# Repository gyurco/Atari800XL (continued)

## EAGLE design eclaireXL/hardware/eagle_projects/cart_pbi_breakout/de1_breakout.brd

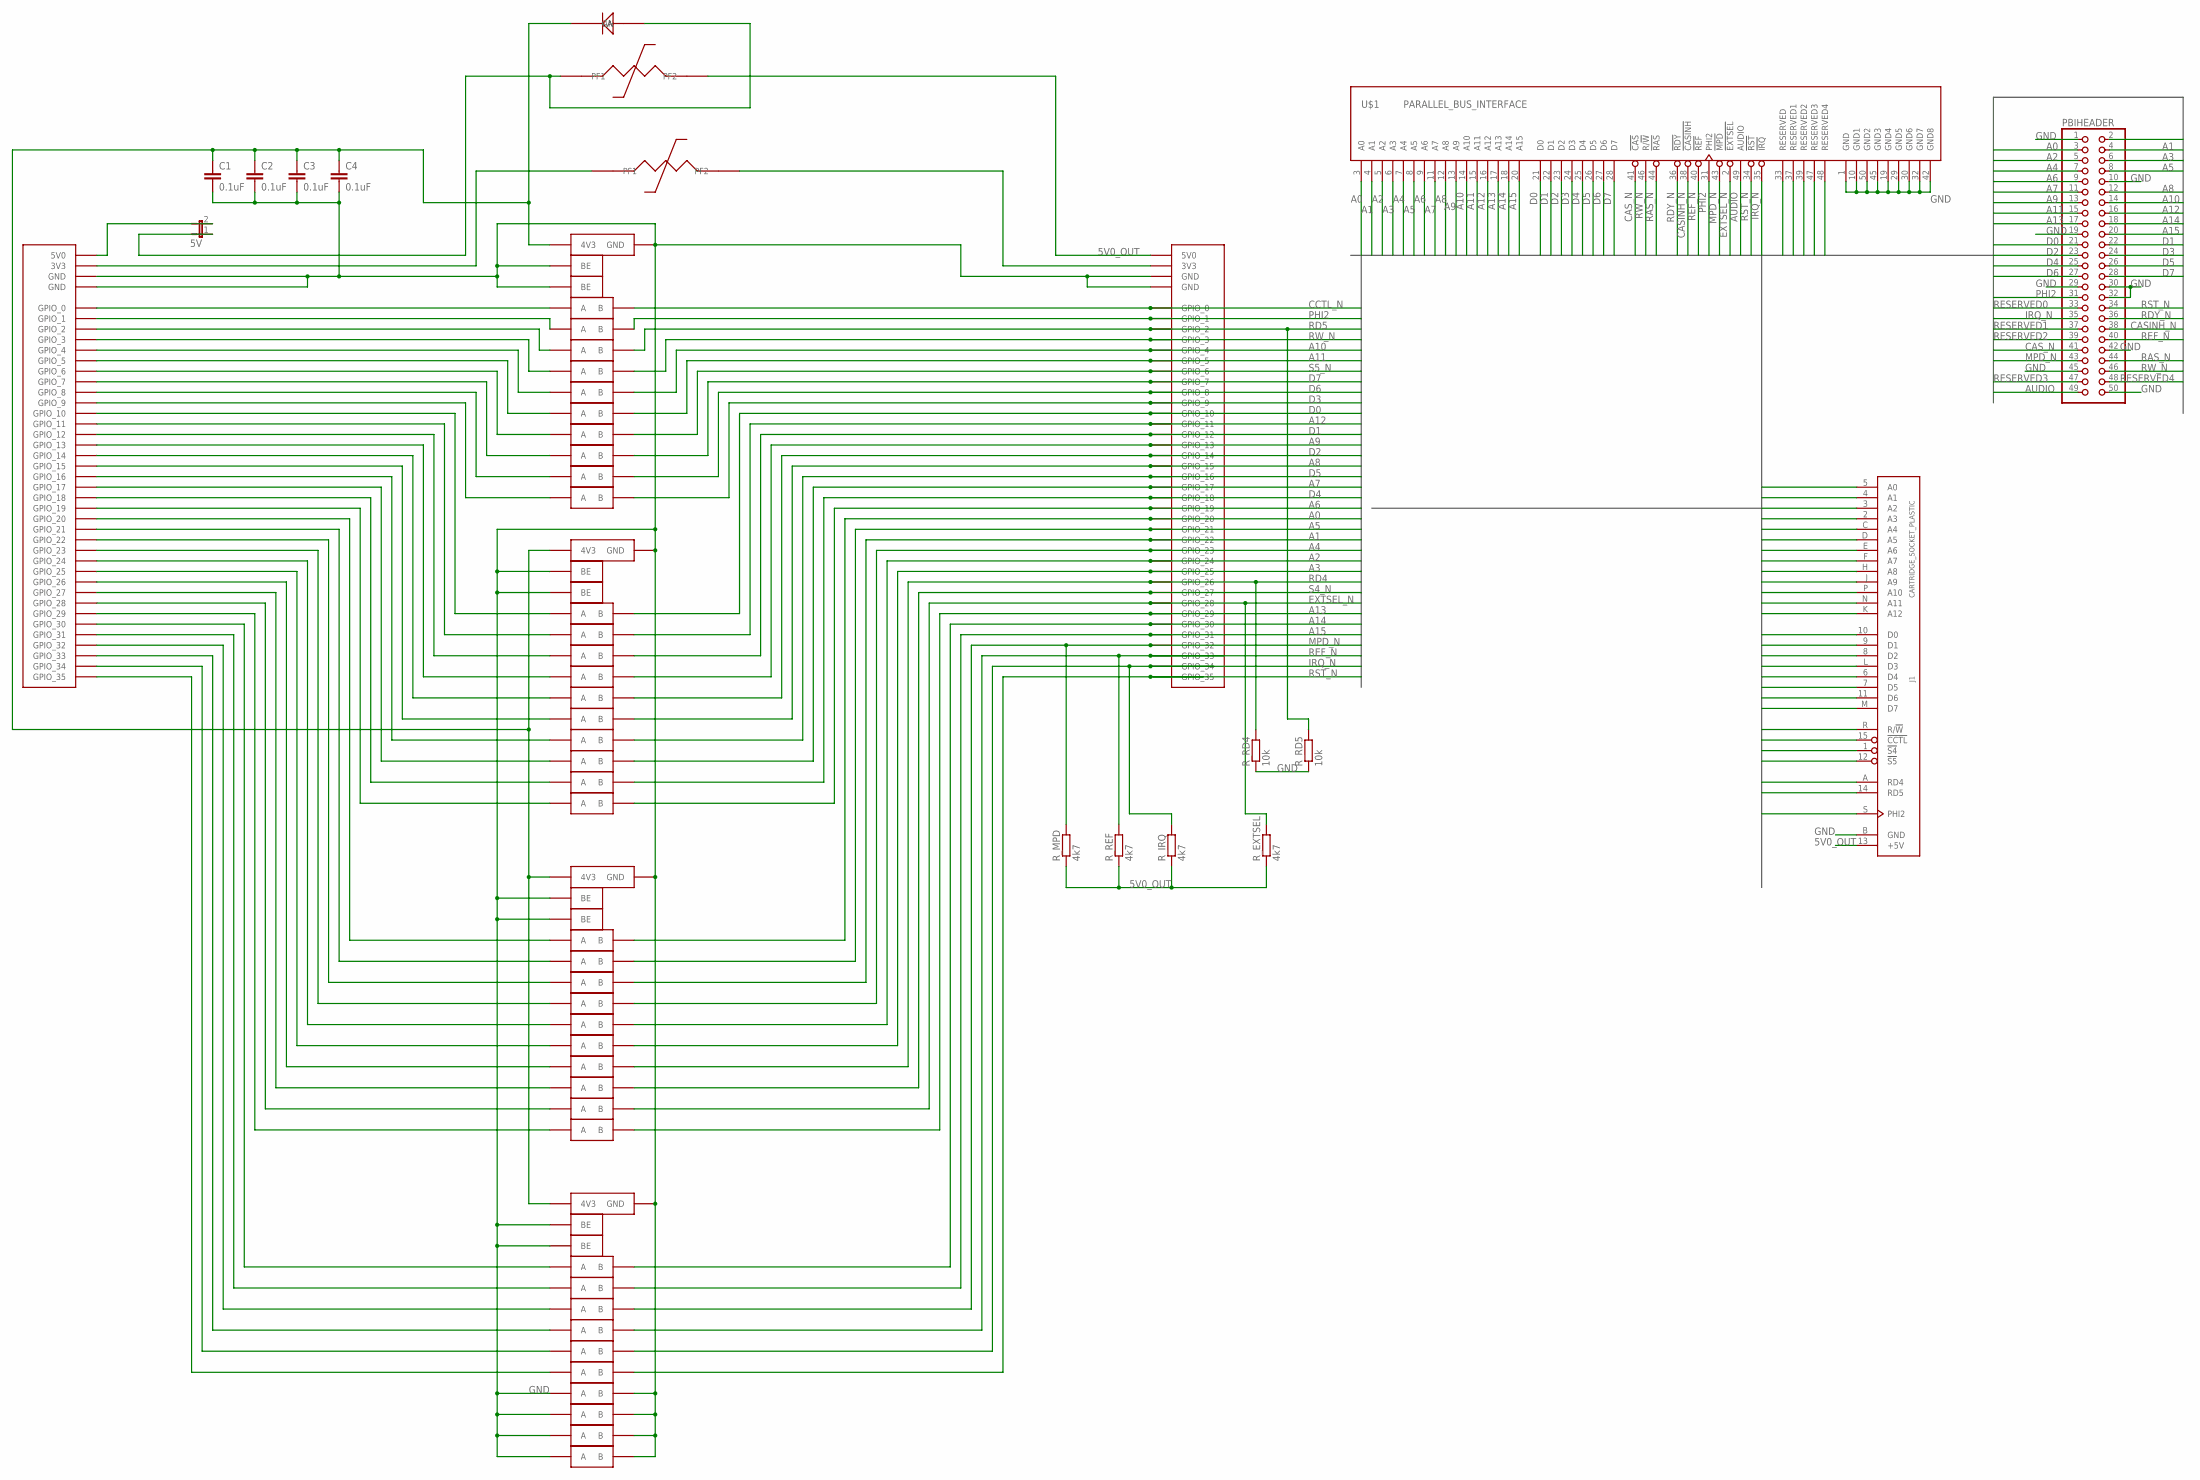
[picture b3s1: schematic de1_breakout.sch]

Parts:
1N4148: 1N4148; SOD123
3VPOLY, 5VPOLY: POLYFUSE_1206; C1206
5V: JP1E; JP1
C1, C2, C3, C4: 0.1uF; C1206
DE1_GPIO: DE1_GPIO; DIL-100-2X20
EXT_GPIO: DE1_GPIO_L; DIL-100-2X20
IC1, IC2, IC3, IC4: QS3384; TSSOP24
J1: CARTRIDGE_SOCKET_PLASTIC; CARTRIDGE_SOCKET_WITH_PLASTIC
PBIHEADER: PINHD-2X25; 2X25
R_EXTSEL: 4k7; R1206
R_IRQ: 4k7; R1206
R_MPD: 4k7; R1206
R_RD4, R_RD5: 10k; R1206
R_REF: 4k7; R1206
U$1: PARALLEL_BUS_INTERFACE

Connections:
3V3_IN: 3VPOLY.1 (PF1), DE1_GPIO.29 (3V3)
3V3_OUT: 3VPOLY.2 (PF2), EXT_GPIO.29 (3V3)
4V3_INT: 1N4148.1 (CA), C1.1, C2.1, C3.1, C4.1, IC1.24 (4V3), IC2.24 (4V3), IC3.24 (4V3), IC4.24 (4V3)
5V0_DE1: 5V.2, DE1_GPIO.11 (5V0)
5V0_IN: 1N4148.2 (AN), 5V.1, 5VPOLY.1 (PF1)
5V0_OUT: 5VPOLY.2 (PF2), EXT_GPIO.11 (5V0), J1.13 (+5V), R_EXTSEL.1, R_IRQ.1, R_MPD.1, R_REF.1
A0: EXT_GPIO.23 (GPIO_20), IC3.2 (B), J1.5 (A0), PBIHEADER.3, U$1.3 (A0)
A1: EXT_GPIO.25 (GPIO_22), IC3.6 (B), J1.4 (A1), PBIHEADER.4, U$1.4 (A1)
A2: EXT_GPIO.27 (GPIO_24), IC3.10 (B), J1.3 (A2), PBIHEADER.5, U$1.5 (A2)
A3: EXT_GPIO.28 (GPIO_25), IC3.15 (B), J1.2 (A3), PBIHEADER.6, U$1.6 (A3)
A4: EXT_GPIO.26 (GPIO_23), IC3.9 (B), J1.C (A4), PBIHEADER.7, U$1.7 (A4)
A5: EXT_GPIO.24 (GPIO_21), IC3.5 (B), J1.D (A5), PBIHEADER.8, U$1.8 (A5)
A6: EXT_GPIO.22 (GPIO_19), IC2.23 (B), J1.E (A6), PBIHEADER.9, U$1.9 (A6)
A7: EXT_GPIO.20 (GPIO_17), IC2.19 (B), J1.F (A7), PBIHEADER.11, U$1.11 (A7)
A8: EXT_GPIO.18 (GPIO_15), IC2.15 (B), J1.H (A8), PBIHEADER.12, U$1.12 (A8)
A9: EXT_GPIO.16 (GPIO_13), IC2.9 (B), J1.J (A9), PBIHEADER.13, U$1.13 (A9)
A10: EXT_GPIO.5 (GPIO_4), IC1.10 (B), J1.P (A10), PBIHEADER.14, U$1.14 (A10)
A11: EXT_GPIO.6 (GPIO_5), IC1.15 (B), J1.N (A11), PBIHEADER.15, U$1.15 (A11)
A12: EXT_GPIO.14 (GPIO_11), IC2.5 (B), J1.K (A12), PBIHEADER.16, U$1.16 (A12)
A13: EXT_GPIO.34 (GPIO_29), IC3.23 (B), PBIHEADER.17, U$1.17 (A13)
A14: EXT_GPIO.35 (GPIO_30), IC4.2 (B), PBIHEADER.18, U$1.18 (A14)
A15: EXT_GPIO.36 (GPIO_31), IC4.5 (B), PBIHEADER.20, U$1.20 (A15)
AUDIO: PBIHEADER.49, U$1.49 (AUDIO)
CASINH_N: PBIHEADER.38, U$1.38 (!CASINH)
CAS_N: PBIHEADER.41, U$1.41 (!CAS)
CCTL_N: EXT_GPIO.1 (GPIO_0), IC1.2 (B), J1.15 (!CCTL)
D0: EXT_GPIO.13 (GPIO_10), IC2.2 (B), J1.10 (D0), PBIHEADER.21, U$1.21 (D0)
D1: EXT_GPIO.15 (GPIO_12), IC2.6 (B), J1.9 (D1), PBIHEADER.22, U$1.22 (D1)
D2: EXT_GPIO.17 (GPIO_14), IC2.10 (B), J1.8 (D2), PBIHEADER.23, U$1.23 (D2)
D3: EXT_GPIO.10 (GPIO_9), IC1.23 (B), J1.L (D3), PBIHEADER.24, U$1.24 (D3)
D4: EXT_GPIO.21 (GPIO_18), IC2.20 (B), J1.6 (D4), PBIHEADER.25, U$1.25 (D4)
D5: EXT_GPIO.19 (GPIO_16), IC2.16 (B), J1.7 (D5), PBIHEADER.26, U$1.26 (D5)
D6: EXT_GPIO.9 (GPIO_8), IC1.20 (B), J1.11 (D6), PBIHEADER.27, U$1.27 (D6)
D7: EXT_GPIO.8 (GPIO_7), IC1.19 (B), J1.M (D7), PBIHEADER.28, U$1.28 (D7)
EXTSEL_N: EXT_GPIO.33 (GPIO_28), IC3.20 (B), PBIHEADER.2, R_EXTSEL.2, U$1.2 (!EXTSEL)
GND: C1.2, C2.2, C3.2, C4.2, DE1_GPIO.12 (GND), DE1_GPIO.30 (GND), EXT_GPIO.12 (GND), EXT_GPIO.30 (GND), IC1.1 (BE), IC1.12 (GND), IC1.13 (BE), IC2.1 (BE), IC2.12 (GND), IC2.13 (BE), IC3.1 (BE), IC3.12 (GND), IC3.13 (BE), IC4.1 (BE), IC4.12 (GND), IC4.13 (BE), IC4.16 (B), IC4.17 (A), IC4.18 (A), IC4.19 (B), IC4.20 (B), IC4.21 (A), IC4.22 (A), IC4.23 (B), J1.B (GND), PBIHEADER.1, PBIHEADER.10, PBIHEADER.19, PBIHEADER.29, PBIHEADER.30, PBIHEADER.32, PBIHEADER.42, PBIHEADER.45, PBIHEADER.50, R_RD4.1, R_RD5.1, U$1.1 (GND), U$1.10 (GND1), U$1.19 (GND4), U$1.29 (GND5), U$1.30 (GND6), U$1.32 (GND7), U$1.42 (GND8), U$1.45 (GND3), U$1.50 (GND2)
IRQ_N: EXT_GPIO.39 (GPIO_34), IC4.10 (B), PBIHEADER.35, R_IRQ.2, U$1.35 (!IRQ)
MPD_N: EXT_GPIO.37 (GPIO_32), IC4.6 (B), PBIHEADER.43, R_MPD.2, U$1.43 (!MPD)
unnamed: DE1_GPIO.1 (GPIO_0), IC1.3 (A)
unnamed: DE1_GPIO.2 (GPIO_1), IC1.4 (A)
unnamed: DE1_GPIO.3 (GPIO_2), IC1.7 (A)
unnamed: DE1_GPIO.4 (GPIO_3), IC1.8 (A)
unnamed: DE1_GPIO.5 (GPIO_4), IC1.11 (A)
unnamed: DE1_GPIO.6 (GPIO_5), IC1.14 (A)
unnamed: DE1_GPIO.7 (GPIO_6), IC1.17 (A)
unnamed: DE1_GPIO.8 (GPIO_7), IC1.18 (A)
unnamed: DE1_GPIO.9 (GPIO_8), IC1.21 (A)
unnamed: DE1_GPIO.10 (GPIO_9), IC1.22 (A)
unnamed: DE1_GPIO.13 (GPIO_10), IC2.3 (A)
unnamed: DE1_GPIO.14 (GPIO_11), IC2.4 (A)
unnamed: DE1_GPIO.15 (GPIO_12), IC2.7 (A)
unnamed: DE1_GPIO.16 (GPIO_13), IC2.8 (A)
unnamed: DE1_GPIO.17 (GPIO_14), IC2.11 (A)
unnamed: DE1_GPIO.18 (GPIO_15), IC2.14 (A)
unnamed: DE1_GPIO.19 (GPIO_16), IC2.17 (A)
unnamed: DE1_GPIO.20 (GPIO_17), IC2.18 (A)
unnamed: DE1_GPIO.21 (GPIO_18), IC2.21 (A)
unnamed: DE1_GPIO.22 (GPIO_19), IC2.22 (A)
unnamed: DE1_GPIO.23 (GPIO_20), IC3.3 (A)
unnamed: DE1_GPIO.24 (GPIO_21), IC3.4 (A)
unnamed: DE1_GPIO.25 (GPIO_22), IC3.7 (A)
unnamed: DE1_GPIO.26 (GPIO_23), IC3.8 (A)
unnamed: DE1_GPIO.27 (GPIO_24), IC3.11 (A)
unnamed: DE1_GPIO.28 (GPIO_25), IC3.14 (A)
unnamed: DE1_GPIO.31 (GPIO_26), IC3.17 (A)
unnamed: DE1_GPIO.32 (GPIO_27), IC3.18 (A)
unnamed: DE1_GPIO.33 (GPIO_28), IC3.21 (A)
unnamed: DE1_GPIO.34 (GPIO_29), IC3.22 (A)
unnamed: DE1_GPIO.37 (GPIO_32), IC4.7 (A)
unnamed: DE1_GPIO.35 (GPIO_30), IC4.3 (A)
unnamed: DE1_GPIO.36 (GPIO_31), IC4.4 (A)
unnamed: DE1_GPIO.38 (GPIO_33), IC4.8 (A)
unnamed: DE1_GPIO.39 (GPIO_34), IC4.11 (A)
unnamed: DE1_GPIO.40 (GPIO_35), IC4.14 (A)
PHI2: EXT_GPIO.2 (GPIO_1), IC1.5 (B), J1.S (PHI2), PBIHEADER.31, U$1.31 (PHI2)
RAS_N: PBIHEADER.44, U$1.44 (!RAS)
RD4: EXT_GPIO.31 (GPIO_26), IC3.16 (B), J1.A (RD4), R_RD4.2
RD5: EXT_GPIO.3 (GPIO_2), IC1.6 (B), J1.14 (RD5), R_RD5.2
RDY_N: PBIHEADER.36, U$1.36 (!RDY)
REF_N: EXT_GPIO.38 (GPIO_33), IC4.9 (B), PBIHEADER.40, R_REF.2, U$1.40 (!REF)
RESERVED0: PBIHEADER.33, U$1.33 (RESERVED)
RESERVED1: PBIHEADER.37, U$1.37 (RESERVED1)
RESERVED2: PBIHEADER.39, U$1.39 (RESERVED2)
RESERVED3: PBIHEADER.47, U$1.47 (RESERVED3)
RESERVED4: PBIHEADER.48, U$1.48 (RESERVED4)
RST_N: EXT_GPIO.40 (GPIO_35), IC4.15 (B), PBIHEADER.34, U$1.34 (!RST)
RW_N: EXT_GPIO.4 (GPIO_3), IC1.9 (B), J1.R (R/!W), PBIHEADER.46, U$1.46 (R/!W)
S4_N: EXT_GPIO.32 (GPIO_27), IC3.19 (B), J1.1 (!S4)
S5_N: EXT_GPIO.7 (GPIO_6), IC1.16 (B), J1.12 (!S5)

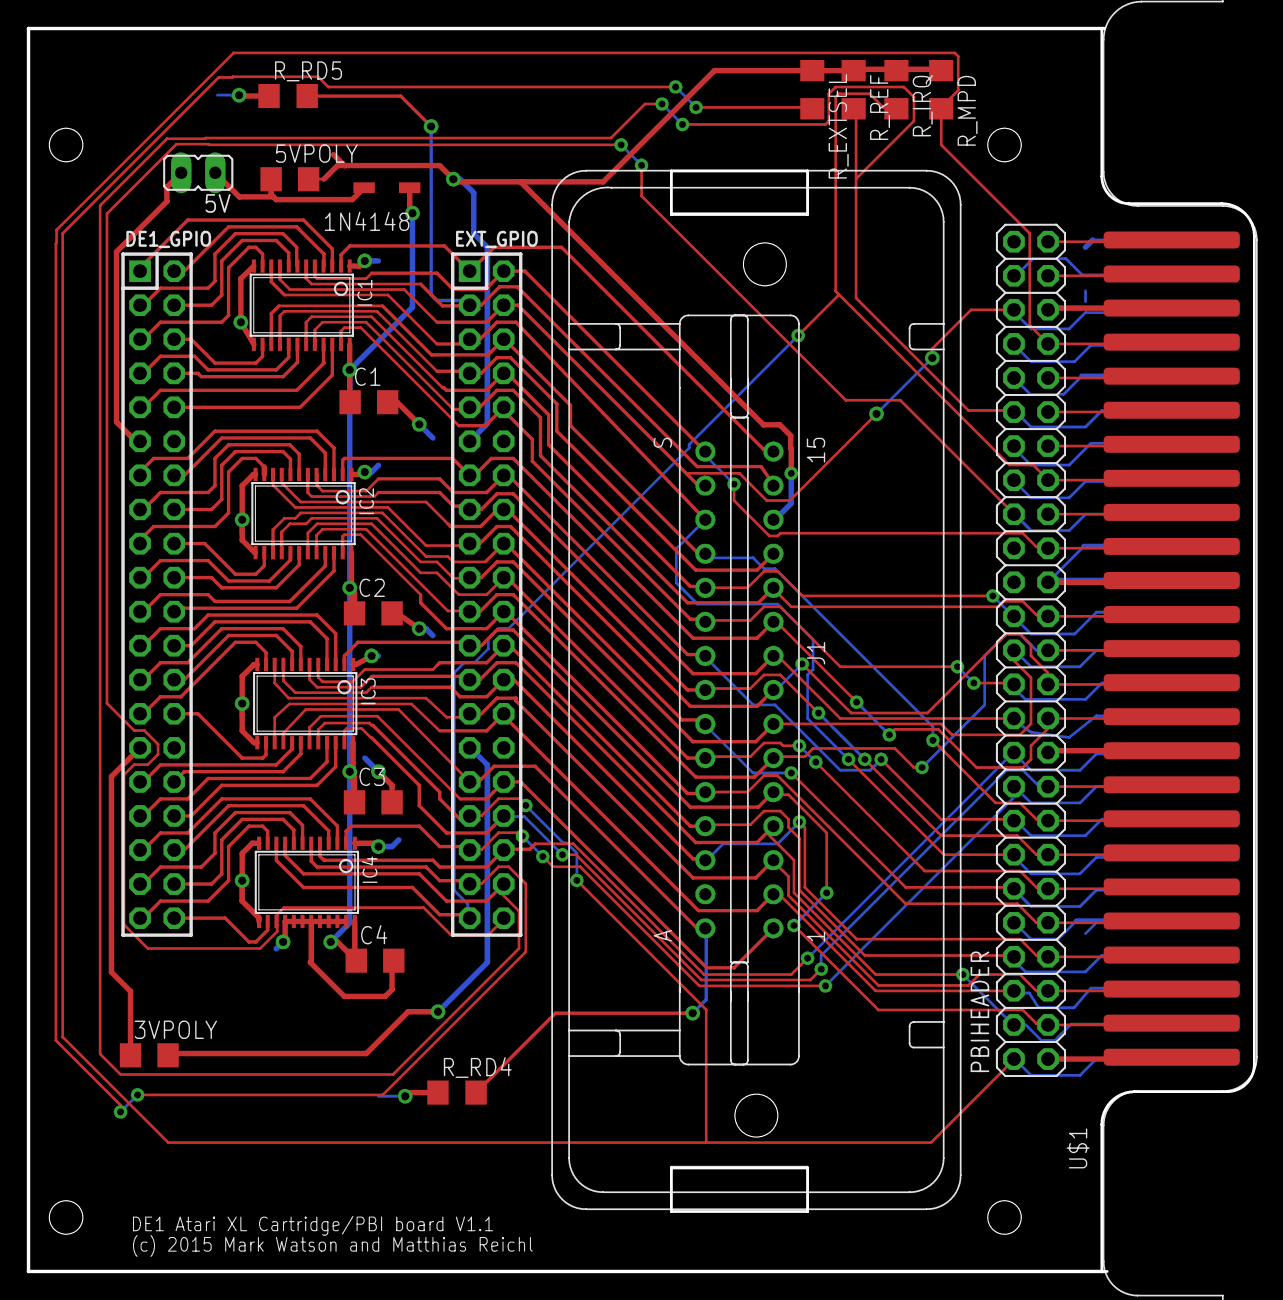
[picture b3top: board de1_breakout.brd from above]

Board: 2 copper layers, 91.4 x 92.7 mm, 23 parts (0 on the bottom side), 89 nets.

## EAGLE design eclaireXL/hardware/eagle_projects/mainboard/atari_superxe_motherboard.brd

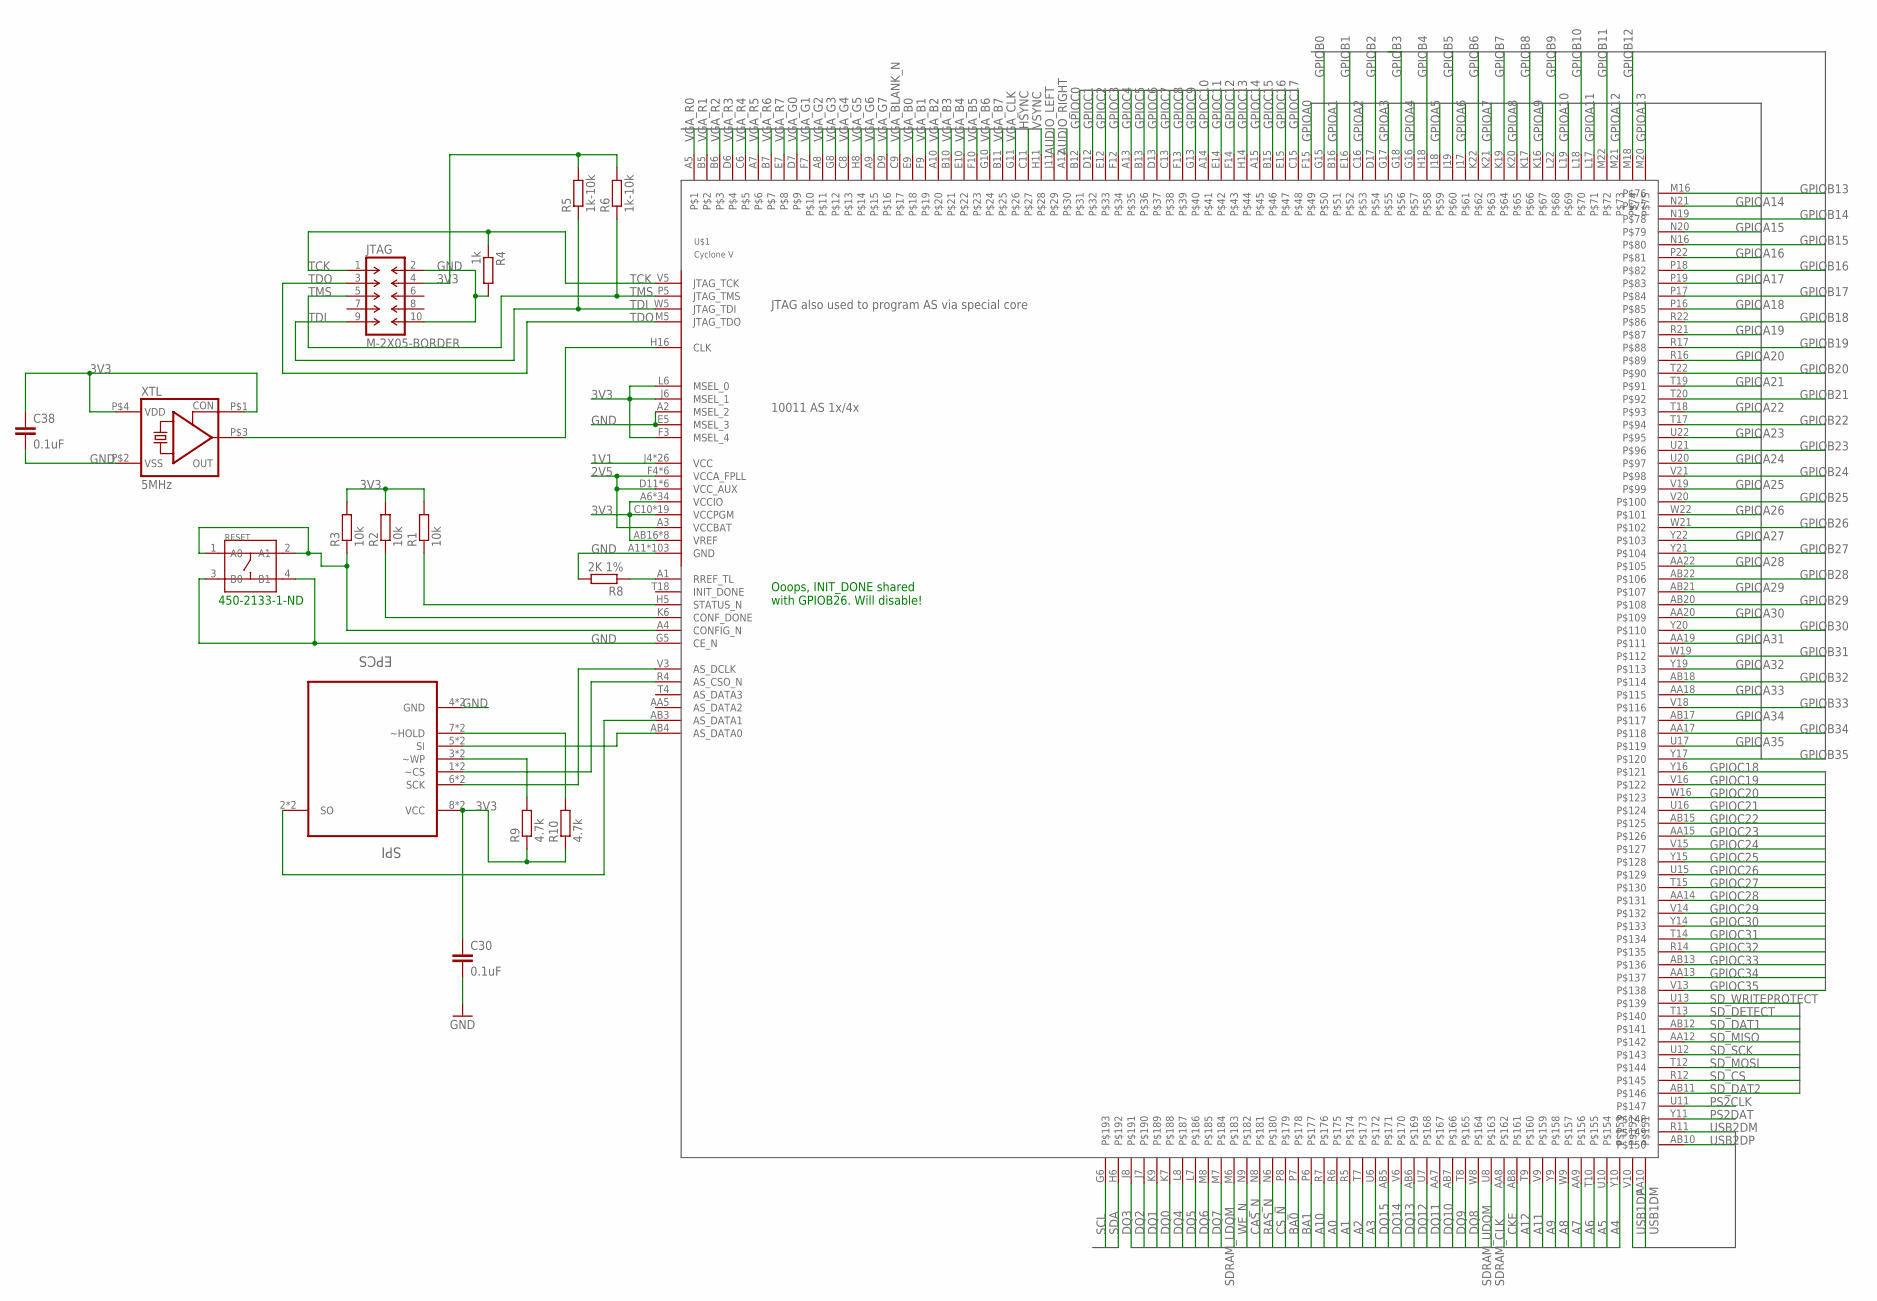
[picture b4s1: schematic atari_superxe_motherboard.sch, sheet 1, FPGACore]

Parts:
C30, C38: 0.1uF; C0805
JTAG: M-2X05-BORDER; DIL-100-2X05-BRD
R1, R2, R3: 10k; M0805
R4: 1k; M0805
R5, R6: 1k-10k; M0805
R8: 2K 1%; M0805
R9, R10: 4.7k; M0805
RESET: SMD-BUTTON(4P-4.0X4.0X1.7MM)-DHT-1152; SW4-SMD-4.0X4.0X1.7MM
SPI: EPCS; EPCS_BOTH
U$1: CYCLONEVFPGA484SMALLPINS; CYCLONEVF484V2
XTL: 5MHz; SG-636

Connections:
1V1: U$1.J4 (VCC), U$1.J10 (VCC), U$1.J12 (VCC), U$1.J14 (VCC), U$1.J16 (VCC), U$1.K3 (VCC), U$1.K5 (VCC), U$1.K11 (VCC), U$1.K13 (VCC), U$1.K15 (VCC), U$1.L4 (VCC), U$1.L10 (VCC), U$1.L12 (VCC), U$1.L14 (VCC), U$1.L16 (VCC), U$1.M11 (VCC), U$1.M13 (VCC), U$1.M15 (VCC), U$1.N4 (VCC), U$1.N10 (VCC), U$1.N12 (VCC), U$1.N14 (VCC), U$1.P3 (VCC), U$1.P11 (VCC), U$1.P13 (VCC), U$1.P15 (VCC); also elsewhere on the board
2V5: U$1.A3 (VCCBAT), U$1.D11 (VCC_AUX), U$1.D18 (VCC_AUX), U$1.E6 (VCC_AUX), U$1.F4 (VCCA_FPLL), U$1.H19 (VCCA_FPLL), U$1.M3 (VCCA_FPLL), U$1.T3 (VCCA_FPLL), U$1.T5 (VCCA_FPLL), U$1.U18 (VCCA_FPLL), U$1.W7 (VCC_AUX), U$1.W13 (VCC_AUX), U$1.W18 (VCC_AUX); also elsewhere on the board
3V3: C30.1, C38.1, JTAG.4, R1.2, R2.2, R3.2, R5.2, R6.2, R9.1, R10.1, SPI.8 (VCC), SPI.L$2 (VCC), U$1.A6 (VCCIO), U$1.A16 (VCCIO), U$1.AA16 (VCCIO), U$1.AA21 (VCCIO), U$1.AB16 (VREF), U$1.B8 (VREF), U$1.B19 (VCCIO), U$1.C7 (VCCIO), U$1.C10 (VCCPGM), U$1.C12 (VCCIO), U$1.C14 (VREF), U$1.C22 (VCCIO), U$1.D4 (VCCIO), U$1.D8 (VCCPGM), U$1.D14 (VCCPGM), U$1.D15 (VCCIO), U$1.D16 (VCCPGM), U$1.E1 (VCCPGM), U$1.E8 (VCCIO), U$1.E11 (VCCPGM), U$1.E18 (VCCIO), U$1.F3 (MSEL_4), U$1.F8 (VCCPGM), U$1.F11 (VCCIO), U$1.F21 (VCCIO), U$1.G7 (VCCIO), U$1.G14 (VCCIO), U$1.H17 (VCCIO), U$1.J1 (VCCIO), U$1.J2 (VCCPGM), U$1.J6 (MSEL_1), U$1.K18 (VCCIO), U$1.L6 (MSEL_0), U$1.L20 (VREF), U$1.M17 (VCCPGM), U$1.M19 (VCCIO), U$1.N18 (VCCPGM), U$1.P20 (VCCIO), U$1.P21 (VCCPGM), U$1.R1 (VCCIO), U$1.R2 (VCCPGM), U$1.R8 (VCCIO), U$1.R18 (VCCIO), U$1.R19 (VCCPGM), U$1.R20 (VREF), U$1.T6 (VCCIO), U$1.T11 (VCCIO), U$1.U14 (VCCIO), U$1.U19 (VCCIO), U$1.V8 (VCCPGM), U$1.W1 (VREF), U$1.W6 (VCCPGM), U$1.W10 (VCCIO), U$1.W11 (VCCPGM), U$1.W12 (VCCPGM), U$1.W14 (VCCPGM), U$1.W15 (VCCIO), U$1.W17 (VCCPGM), U$1.W20 (VCCIO), U$1.Y4 (VCCIO), U$1.Y7 (VREF), U$1.Y8 (VCCIO), U$1.Y12 (VREF), U$1.Y13 (VCCIO), XTL.P$1 (CON), XTL.P$4 (VDD); also elsewhere on the board
A0: U$1.R6; also elsewhere on the board
A1: U$1.R5; also elsewhere on the board
A2: U$1.T7; also elsewhere on the board
A3: U$1.U6; also elsewhere on the board
A4: U$1.Y10; also elsewhere on the board
A5: U$1.U10; also elsewhere on the board
A6: U$1.T10; also elsewhere on the board
A7: U$1.AA9; also elsewhere on the board
A8: U$1.W9; also elsewhere on the board
A9: U$1.Y9; also elsewhere on the board
A10: U$1.R7; also elsewhere on the board
A11: U$1.V9; also elsewhere on the board
A12: U$1.T9; also elsewhere on the board
AUDIO_LEFT: U$1.J11; also elsewhere on the board
AUDIO_RIGHT: U$1.A12; also elsewhere on the board
BA0: U$1.P7; also elsewhere on the board
BA1: U$1.P6; also elsewhere on the board
CAS_N: U$1.N8; also elsewhere on the board
CKE: U$1.AB8; also elsewhere on the board
CONFIG_N: R3.1, RESET.1 (A0), RESET.2 (A1), U$1.A4 (CONFIG_N)
CONF_DONE: R2.1, U$1.K6 (CONF_DONE)
CS_N: U$1.P8; also elsewhere on the board
DQ0: U$1.K7; also elsewhere on the board
DQ1: U$1.K9; also elsewhere on the board
DQ2: U$1.J7; also elsewhere on the board
DQ3: U$1.J8; also elsewhere on the board
DQ4: U$1.L8; also elsewhere on the board
DQ5: U$1.L7; also elsewhere on the board
DQ6: U$1.M8; also elsewhere on the board
DQ7: U$1.M7; also elsewhere on the board
DQ8: U$1.W8; also elsewhere on the board
DQ9: U$1.T8; also elsewhere on the board
DQ10: U$1.AB7; also elsewhere on the board
DQ11: U$1.AA7; also elsewhere on the board
DQ12: U$1.U7; also elsewhere on the board
DQ13: U$1.AB6; also elsewhere on the board
DQ14: U$1.V6; also elsewhere on the board
DQ15: U$1.AB5; also elsewhere on the board
GND: C30.2, C38.2, JTAG.2, JTAG.10, R4.2, R8.2, RESET.3 (B0), RESET.4 (B1), SPI.4 (GND), SPI.L$10 (GND), U$1.A2 (MSEL_2), U$1.A11 (GND), U$1.A21 (GND), U$1.AA3 (GND), U$1.AA4 (GND), U$1.AA6 (GND), U$1.AA11 (GND), U$1.AB1 (GND), U$1.AB2 (GND), U$1.AB9 (GND), U$1.AB14 (GND), U$1.AB19 (GND), U$1.B1 (GND), U$1.B2 (GND), U$1.B9 (GND), U$1.B14 (GND), U$1.C3 (GND), U$1.C4 (GND), U$1.C5 (GND), U$1.C17 (GND), U$1.D1 (GND), U$1.D2 (GND), U$1.D5 (GND), U$1.D10 (GND), U$1.D20 (GND), U$1.E3 (GND), U$1.E4 (GND), U$1.E5 (MSEL_3), U$1.E13 (GND), U$1.F1 (GND), U$1.F2 (GND), U$1.F5 (GND), U$1.F6 (GND), U$1.F16 (GND), U$1.F17 (GND), U$1.G3 (GND), U$1.G4 (GND), U$1.G5 (CE_N), U$1.G9 (GND), U$1.G19 (GND), U$1.H1 (GND), U$1.H2 (GND), U$1.H3 (GND), U$1.H4 (GND), U$1.H7 (GND), U$1.H12 (GND), U$1.H15 (GND), U$1.H22 (GND), U$1.J3 (GND), U$1.J5 (GND), U$1.J15 (GND), U$1.J20 (GND), U$1.K1 (GND), U$1.K2 (GND), U$1.K4 (GND), U$1.K8 (GND), U$1.K10 (GND), U$1.K12 (GND), U$1.K14 (GND), U$1.L3 (GND), U$1.L5 (GND), U$1.L11 (GND), U$1.L13 (GND), U$1.L15 (GND), U$1.L21 (GND), U$1.M1 (GND), U$1.M2 (GND), U$1.M4 (GND), U$1.M10 (GND), U$1.M12 (GND), U$1.M14 (GND), U$1.N3 (GND), U$1.N5 (GND), U$1.N7 (GND), U$1.N11 (GND), U$1.N13 (GND), U$1.N15 (GND), U$1.N17 (GND), U$1.N22 (GND), U$1.P1 (GND), U$1.P2 (GND), U$1.P4 (GND), U$1.P10 (GND), U$1.R3 (GND), U$1.R13 (GND), U$1.T1 (GND), U$1.T2 (GND), U$1.T16 (GND), U$1.T21 (GND), U$1.U3 (GND), U$1.U4 (GND), U$1.U5 (GND), U$1.U9 (GND), U$1.V1 (GND), U$1.V2 (GND), U$1.V4 (GND), U$1.V7 (GND), U$1.V12 (GND), U$1.V17 (GND), U$1.V22 (GND), U$1.W3 (GND), U$1.W4 (GND), U$1.Y1 (GND), U$1.Y2 (GND), U$1.Y5 (GND), U$1.Y18 (GND), XTL.P$2 (VSS); also elsewhere on the board
GPIOA0: U$1.F15; also elsewhere on the board
GPIOA1: U$1.B16; also elsewhere on the board
GPIOA2: U$1.C16; also elsewhere on the board
GPIOA3: U$1.G17; also elsewhere on the board
GPIOA4: U$1.G16; also elsewhere on the board
GPIOA5: U$1.J18; also elsewhere on the board
GPIOA6: U$1.J17; also elsewhere on the board
GPIOA7: U$1.K21; also elsewhere on the board
GPIOA8: U$1.K20; also elsewhere on the board
GPIOA9: U$1.K16; also elsewhere on the board
GPIOA10: U$1.L19; also elsewhere on the board
GPIOA11: U$1.L17; also elsewhere on the board
GPIOA12: U$1.M21; also elsewhere on the board
GPIOA13: U$1.M20; also elsewhere on the board
GPIOA14: U$1.N21; also elsewhere on the board
GPIOA15: U$1.N20; also elsewhere on the board
GPIOA16: U$1.P22; also elsewhere on the board
GPIOA17: U$1.P19; also elsewhere on the board
GPIOA18: U$1.P16; also elsewhere on the board
GPIOA19: U$1.R21; also elsewhere on the board
GPIOA20: U$1.R16; also elsewhere on the board
GPIOA21: U$1.T19; also elsewhere on the board
GPIOA22: U$1.T18; also elsewhere on the board
GPIOA23: U$1.U22; also elsewhere on the board
GPIOA24: U$1.U20; also elsewhere on the board
GPIOA25: U$1.V19; also elsewhere on the board
GPIOA26: U$1.W22; also elsewhere on the board
GPIOA27: U$1.Y22; also elsewhere on the board
GPIOA28: U$1.AA22; also elsewhere on the board
GPIOA29: U$1.AB21; also elsewhere on the board
GPIOA30: U$1.AA20; also elsewhere on the board
GPIOA31: U$1.AA19; also elsewhere on the board
GPIOA32: U$1.Y19; also elsewhere on the board
GPIOA33: U$1.AA18; also elsewhere on the board
GPIOA34: U$1.AB17; also elsewhere on the board
GPIOA35: U$1.U17; also elsewhere on the board
GPIOB0: U$1.G15; also elsewhere on the board
GPIOB1: U$1.E16; also elsewhere on the board
GPIOB2: U$1.D17; also elsewhere on the board
GPIOB3: U$1.G18; also elsewhere on the board
GPIOB4: U$1.H18; also elsewhere on the board
GPIOB5: U$1.J19; also elsewhere on the board
GPIOB6: U$1.K22; also elsewhere on the board
GPIOB7: U$1.K19; also elsewhere on the board
GPIOB8: U$1.K17; also elsewhere on the board
GPIOB9: U$1.L22; also elsewhere on the board
GPIOB10: U$1.L18; also elsewhere on the board
GPIOB11: U$1.M22; also elsewhere on the board
GPIOB12: U$1.M18; also elsewhere on the board
GPIOB13: U$1.M16; also elsewhere on the board
GPIOB14: U$1.N19; also elsewhere on the board
GPIOB15: U$1.N16; also elsewhere on the board
GPIOB16: U$1.P18; also elsewhere on the board
GPIOB17: U$1.P17; also elsewhere on the board
GPIOB18: U$1.R22; also elsewhere on the board
GPIOB19: U$1.R17; also elsewhere on the board
GPIOB20: U$1.T22; also elsewhere on the board
GPIOB21: U$1.T20; also elsewhere on the board
GPIOB22: U$1.T17; also elsewhere on the board
GPIOB23: U$1.U21; also elsewhere on the board
GPIOB24: U$1.V21; also elsewhere on the board
GPIOB25: U$1.V20; also elsewhere on the board
GPIOB26: U$1.W21; also elsewhere on the board
GPIOB27: U$1.Y21; also elsewhere on the board
GPIOB28: U$1.AB22; also elsewhere on the board
GPIOB29: U$1.AB20; also elsewhere on the board
GPIOB30: U$1.Y20; also elsewhere on the board
GPIOB31: U$1.W19; also elsewhere on the board
GPIOB32: U$1.AB18; also elsewhere on the board
GPIOB33: U$1.V18; also elsewhere on the board
GPIOB34: U$1.AA17; also elsewhere on the board
GPIOB35: U$1.Y17; also elsewhere on the board
GPIOC0: U$1.B12; also elsewhere on the board
GPIOC1: U$1.D12; also elsewhere on the board
GPIOC2: U$1.E12; also elsewhere on the board
GPIOC3: U$1.F12; also elsewhere on the board
GPIOC4: U$1.A13; also elsewhere on the board
GPIOC5: U$1.B13; also elsewhere on the board
GPIOC6: U$1.D13; also elsewhere on the board
GPIOC7: U$1.C13; also elsewhere on the board
GPIOC8: U$1.F13; also elsewhere on the board
GPIOC9: U$1.G13; also elsewhere on the board
GPIOC10: U$1.A14; also elsewhere on the board
GPIOC11: U$1.E14; also elsewhere on the board
GPIOC12: U$1.F14; also elsewhere on the board
GPIOC13: U$1.H14; also elsewhere on the board
GPIOC14: U$1.A15; also elsewhere on the board
GPIOC15: U$1.B15; also elsewhere on the board
GPIOC16: U$1.E15; also elsewhere on the board
GPIOC17: U$1.C15; also elsewhere on the board
GPIOC18: U$1.Y16; also elsewhere on the board
GPIOC19: U$1.V16; also elsewhere on the board
GPIOC20: U$1.W16; also elsewhere on the board
GPIOC21: U$1.U16; also elsewhere on the board
GPIOC22: U$1.AB15; also elsewhere on the board
GPIOC23: U$1.AA15; also elsewhere on the board
GPIOC24: U$1.V15; also elsewhere on the board
GPIOC25: U$1.Y15; also elsewhere on the board
GPIOC26: U$1.U15; also elsewhere on the board
GPIOC27: U$1.T15; also elsewhere on the board
GPIOC28: U$1.AA14; also elsewhere on the board
GPIOC29: U$1.V14; also elsewhere on the board
GPIOC30: U$1.Y14; also elsewhere on the board
GPIOC31: U$1.T14; also elsewhere on the board
GPIOC32: U$1.R14; also elsewhere on the board
GPIOC33: U$1.AB13; also elsewhere on the board
GPIOC34: U$1.AA13; also elsewhere on the board
GPIOC35: U$1.V13; also elsewhere on the board
HSYNC: U$1.C11; also elsewhere on the board
unnamed: SPI.6 (SCK), SPI.L$16 (SCK), U$1.V3 (AS_DCLK)
unnamed: SPI.1 (~CS), SPI.L$7 (~CS), U$1.R4 (AS_CSO_N)
unnamed: SPI.2 (SO), SPI.L$8 (SO), U$1.AB3 (AS_DATA1)
unnamed: SPI.5 (SI), SPI.L$15 (SI), U$1.AB4 (AS_DATA0)
unnamed: R9.2, SPI.3 (~WP), SPI.L$9 (~WP)
unnamed: R10.2, SPI.7 (~HOLD), SPI.L$1 (~HOLD)
unnamed: U$1.H16 (CLK), XTL.P$3 (OUT)
PS2CLK: U$1.U11; also elsewhere on the board
PS2DAT: U$1.Y11; also elsewhere on the board
RAS_N: U$1.N6; also elsewhere on the board
RREF_TL: R8.1, U$1.A1 (RREF_TL)
SCL: U$1.G6; also elsewhere on the board
SDA: U$1.H6; also elsewhere on the board
SDRAM_CLK: U$1.AA8; also elsewhere on the board
SDRAM_LDQM: U$1.M6; also elsewhere on the board
SDRAM_UDQM: U$1.U8; also elsewhere on the board
SD_CS: U$1.R12; also elsewhere on the board
SD_DAT1: U$1.AB12; also elsewhere on the board
SD_DAT2: U$1.AB11; also elsewhere on the board
SD_DETECT: U$1.T13; also elsewhere on the board
SD_MISO: U$1.AA12; also elsewhere on the board
SD_MOSI: U$1.T12; also elsewhere on the board
SD_SCK: U$1.U12; also elsewhere on the board
SD_WRITEPROTECT: U$1.U13; also elsewhere on the board
STATUS_N: R1.1, U$1.H5 (STATUS_N)
TCK: JTAG.1, R4.1, U$1.V5 (JTAG_TCK)
TDI: JTAG.9, R5.1, U$1.W5 (JTAG_TDI)
TDO: JTAG.3, U$1.M5 (JTAG_TDO)
TMS: JTAG.5, R6.1, U$1.P5 (JTAG_TMS)
USB1DM: U$1.AA10; also elsewhere on the board
USB1DP: U$1.V10; also elsewhere on the board
USB2DM: U$1.R11; also elsewhere on the board
USB2DP: U$1.AB10; also elsewhere on the board
VGA_B0: U$1.E9; also elsewhere on the board
VGA_B1: U$1.F9; also elsewhere on the board
VGA_B2: U$1.A10; also elsewhere on the board
VGA_B3: U$1.B10; also elsewhere on the board
VGA_B4: U$1.E10; also elsewhere on the board
VGA_B5: U$1.F10; also elsewhere on the board
VGA_B6: U$1.G10; also elsewhere on the board
VGA_B7: U$1.B11; also elsewhere on the board
VGA_BLANK_N: U$1.C9; also elsewhere on the board
VGA_CLK: U$1.G11; also elsewhere on the board
VGA_G0: U$1.D7; also elsewhere on the board
VGA_G1: U$1.F7; also elsewhere on the board
VGA_G2: U$1.A8; also elsewhere on the board
VGA_G3: U$1.G8; also elsewhere on the board
VGA_G4: U$1.C8; also elsewhere on the board
VGA_G5: U$1.H8; also elsewhere on the board
VGA_G6: U$1.A9; also elsewhere on the board
VGA_G7: U$1.D9; also elsewhere on the board
VGA_R0: U$1.A5; also elsewhere on the board
VGA_R1: U$1.B5; also elsewhere on the board
VGA_R2: U$1.B6; also elsewhere on the board
VGA_R3: U$1.D6; also elsewhere on the board
VGA_R4: U$1.C6; also elsewhere on the board
VGA_R5: U$1.A7; also elsewhere on the board
VGA_R6: U$1.B7; also elsewhere on the board
VGA_R7: U$1.E7; also elsewhere on the board
VSYNC: U$1.H11; also elsewhere on the board
WE_N: U$1.N9; also elsewhere on the board

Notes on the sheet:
10011 AS 1x/4x
JTAG also used to program AS via special core
Ooops, INIT_DONE shared with GPIOB26. Will disable!
450-2133-1-ND

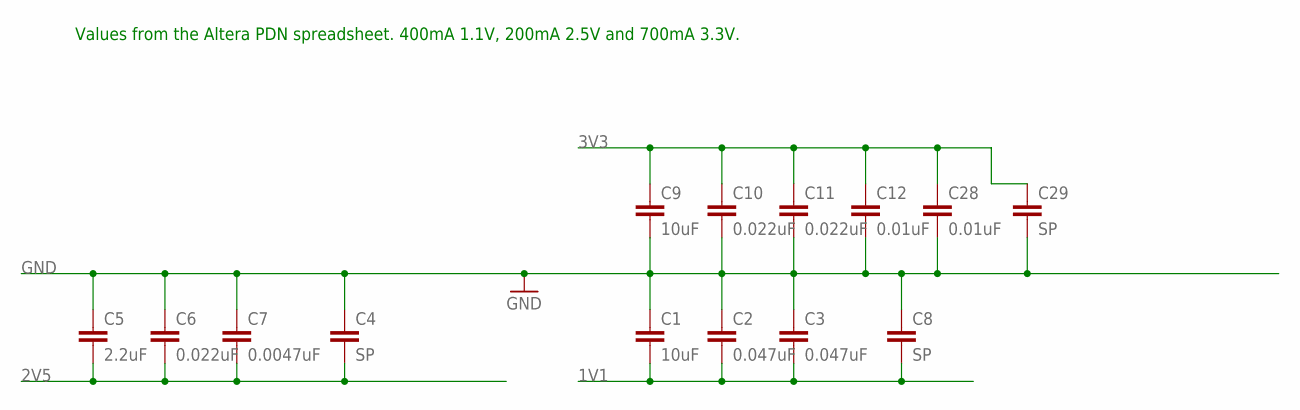
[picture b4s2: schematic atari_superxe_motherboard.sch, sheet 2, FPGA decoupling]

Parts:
C1, C9: 10uF; C0805
C2, C3: 0.047uF; C0805
C4, C8, C29: SP; C0805
C5: 2.2uF; C0805
C6, C10, C11: 0.022uF; C0805
C7: 0.0047uF; C0805
C12, C28: 0.01uF; C0805

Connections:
1V1: C1.2, C2.2, C3.2, C8.2; also elsewhere on the board
2V5: C4.2, C5.2, C6.2, C7.2; also elsewhere on the board
3V3: C9.1, C10.1, C11.1, C12.1, C28.1, C29.1; also elsewhere on the board
GND: C1.1, C2.1, C3.1, C4.1, C5.1, C6.1, C7.1, C8.1, C9.2, C10.2, C11.2, C12.2, C28.2, C29.2; also elsewhere on the board

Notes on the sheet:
Values from the Altera PDN spreadsheet. 400mA 1.1V, 200mA 2.5V and 700mA 3.3V.
